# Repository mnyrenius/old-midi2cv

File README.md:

# old-midi2cv

PCB design + software for a midi2cv eurorack module.

I created it in 2016 and it has been installed in my rack since then.
It doesn't have any cool features and is probably really crappy, but it kind of works.

## Schematics

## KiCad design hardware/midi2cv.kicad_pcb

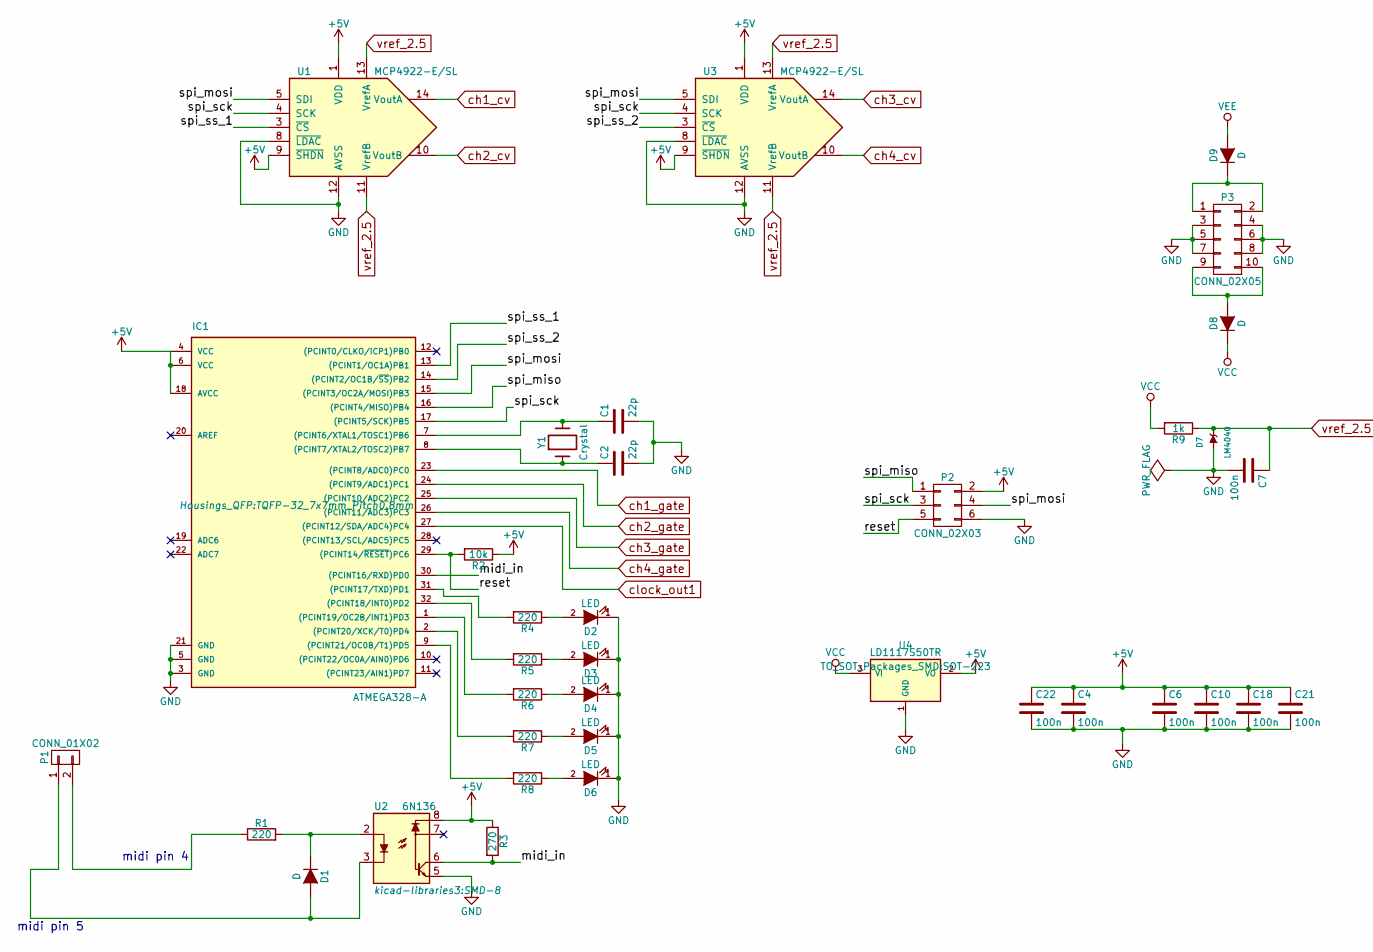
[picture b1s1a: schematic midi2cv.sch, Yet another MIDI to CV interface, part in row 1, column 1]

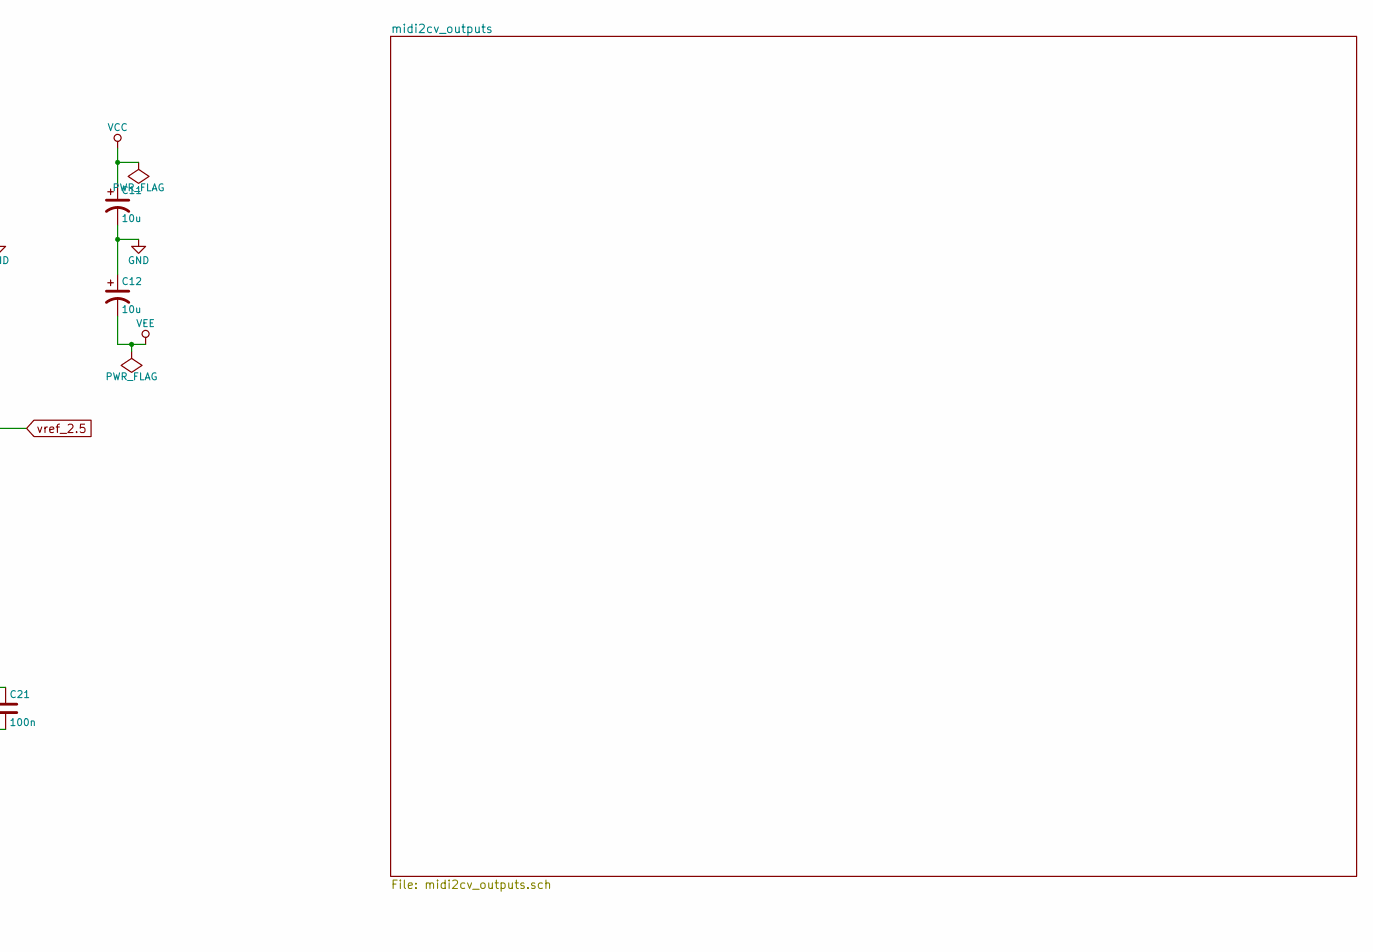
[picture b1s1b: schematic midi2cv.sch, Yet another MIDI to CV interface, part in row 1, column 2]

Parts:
C1, C2: 22p; C_0603_HandSoldering
C4, C6, C7, C10, C18, C21, C22: 100n; C_0603_HandSoldering
C11, C12: 10u; c_elec_4x5.3
D1, D8, D9: D; SOD123
D2, D3, D4, D5, D6: LED; LED-3MM
D7: LM4040; SOT-23
IC1: ATMEGA328-A; TQFP-32_7x7mm_Pitch0.8mm
P1: CONN_01X02; Pin_Header_Straight_1x02
P2: CONN_02X03; Pin_Header_Straight_2x03
P3: CONN_02X05; Pin_Header_Straight_2x05
R1, R4, R5, R6, R7, R8: 220; R_0603_HandSoldering
R2: 10k; R_0603_HandSoldering
R3: 270; R_0603_HandSoldering
R9: 1k; R_0603_HandSoldering
U1, U3: MCP4922-E/SL; SOIC-14_N
U2: 6N136; SMD-8
U4: LD1117S50TR; SOT-223
Y1: Crystal; Crystal_HC49-SD_SMD

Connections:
+5V: C4.1, C6.1, C10.1, C18.1, C21.1, C22.1, IC1.4 (VCC), IC1.6 (VCC), IC1.18 (AVCC), P2.2, R2.1, R3.1, U1.1 (VDD), U1.9 (~SHDN~), U2.8, U3.1 (VDD), U3.9 (~SHDN~), U4.2 (VO)
/midi_in: IC1.30 ((PCINT16/RXD)PD0), R3.2, U2.6
/reset: IC1.29 ((PCINT14/~RESET~)PC6), P2.5, R2.2
/spi_miso: IC1.16 ((PCINT4/MISO)PB4), P2.1
/spi_mosi: IC1.15 ((PCINT3/OC2A/MOSI)PB3), P2.4, U1.5 (SDI), U3.5 (SDI)
/spi_sck: IC1.17 ((PCINT5/SCK)PB5), P2.3, U1.4 (SCK), U3.4 (SCK)
/spi_ss_1: IC1.13 ((PCINT1/OC1A)PB1), U1.3 (~CS~)
/spi_ss_2: IC1.14 ((PCINT2/OC1B/~SS~)PB2), U3.3 (~CS~)
GND: C1.2, C2.2, C4.2, C6.2, C7.2, C10.2, C11.2, C12.1, C18.2, C21.2, C22.2, D2.1 (K), D3.1 (K), D4.1 (K), D5.1 (K), D6.1 (K), D7.2 (A), IC1.3 (GND), IC1.5 (GND), IC1.21 (GND), P2.6, P3.3, P3.4, P3.5, P3.6, P3.7, P3.8, U1.8 (~LDAC~), U1.12 (AVSS), U2.5, U3.8 (~LDAC~), U3.12 (AVSS), U4.1 (GND); also elsewhere on the board
unnamed: C1.1, IC1.7 ((PCINT6/XTAL1/TOSC1)PB6), Y1.2
unnamed: C2.1, IC1.8 ((PCINT7/XTAL2/TOSC2)PB7), Y1.1
unnamed: D1.1 (K), R1.2, U2.2
unnamed: D1.2 (A), P1.1, U2.3
unnamed: D2.2 (A), R4.1
unnamed: D3.2 (A), R5.1
unnamed: D4.2 (A), R6.1
unnamed: D5.2 (A), R7.1
unnamed: D6.2 (A), R8.1
unnamed: D8.2 (A), P3.9, P3.10
unnamed: D9.1 (K), P3.1, P3.2
unnamed: IC1.1 ((PCINT19/OC2B/INT1)PD3), R6.2
unnamed: IC1.2 ((PCINT20/XCK/T0)PD4), R7.2
unnamed: IC1.9 ((PCINT21/OC0B/T1)PD5), R8.2
unnamed: IC1.31 ((PCINT17/TXD)PD1), R4.2
unnamed: IC1.32 ((PCINT18/INT0)PD2), R5.2
unnamed: P1.2, R1.1
VCC: C11.1, D8.1 (K), R9.2, U4.3 (VI); also elsewhere on the board
VEE: C12.2, D9.2 (A); also elsewhere on the board
ch1_cv: U1.14 (VoutA); also elsewhere on the board
ch1_gate: IC1.23 ((PCINT8/ADC0)PC0); also elsewhere on the board
ch2_cv: U1.10 (VoutB); also elsewhere on the board
ch2_gate: IC1.24 ((PCINT9/ADC1)PC1); also elsewhere on the board
ch3_cv: U3.14 (VoutA); also elsewhere on the board
ch3_gate: IC1.25 ((PCINT10/ADC2)PC2); also elsewhere on the board
ch4_cv: U3.10 (VoutB); also elsewhere on the board
ch4_gate: IC1.26 ((PCINT11/ADC3)PC3); also elsewhere on the board
clock_out1: IC1.27 ((PCINT12/SDA/ADC4)PC4); also elsewhere on the board
vref_2.5: C7.1, D7.1 (K), R9.1, U1.11 (VrefB), U1.13 (VrefA), U3.11 (VrefB), U3.13 (VrefA); also elsewhere on the board

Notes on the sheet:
midi pin 4
midi pin 5

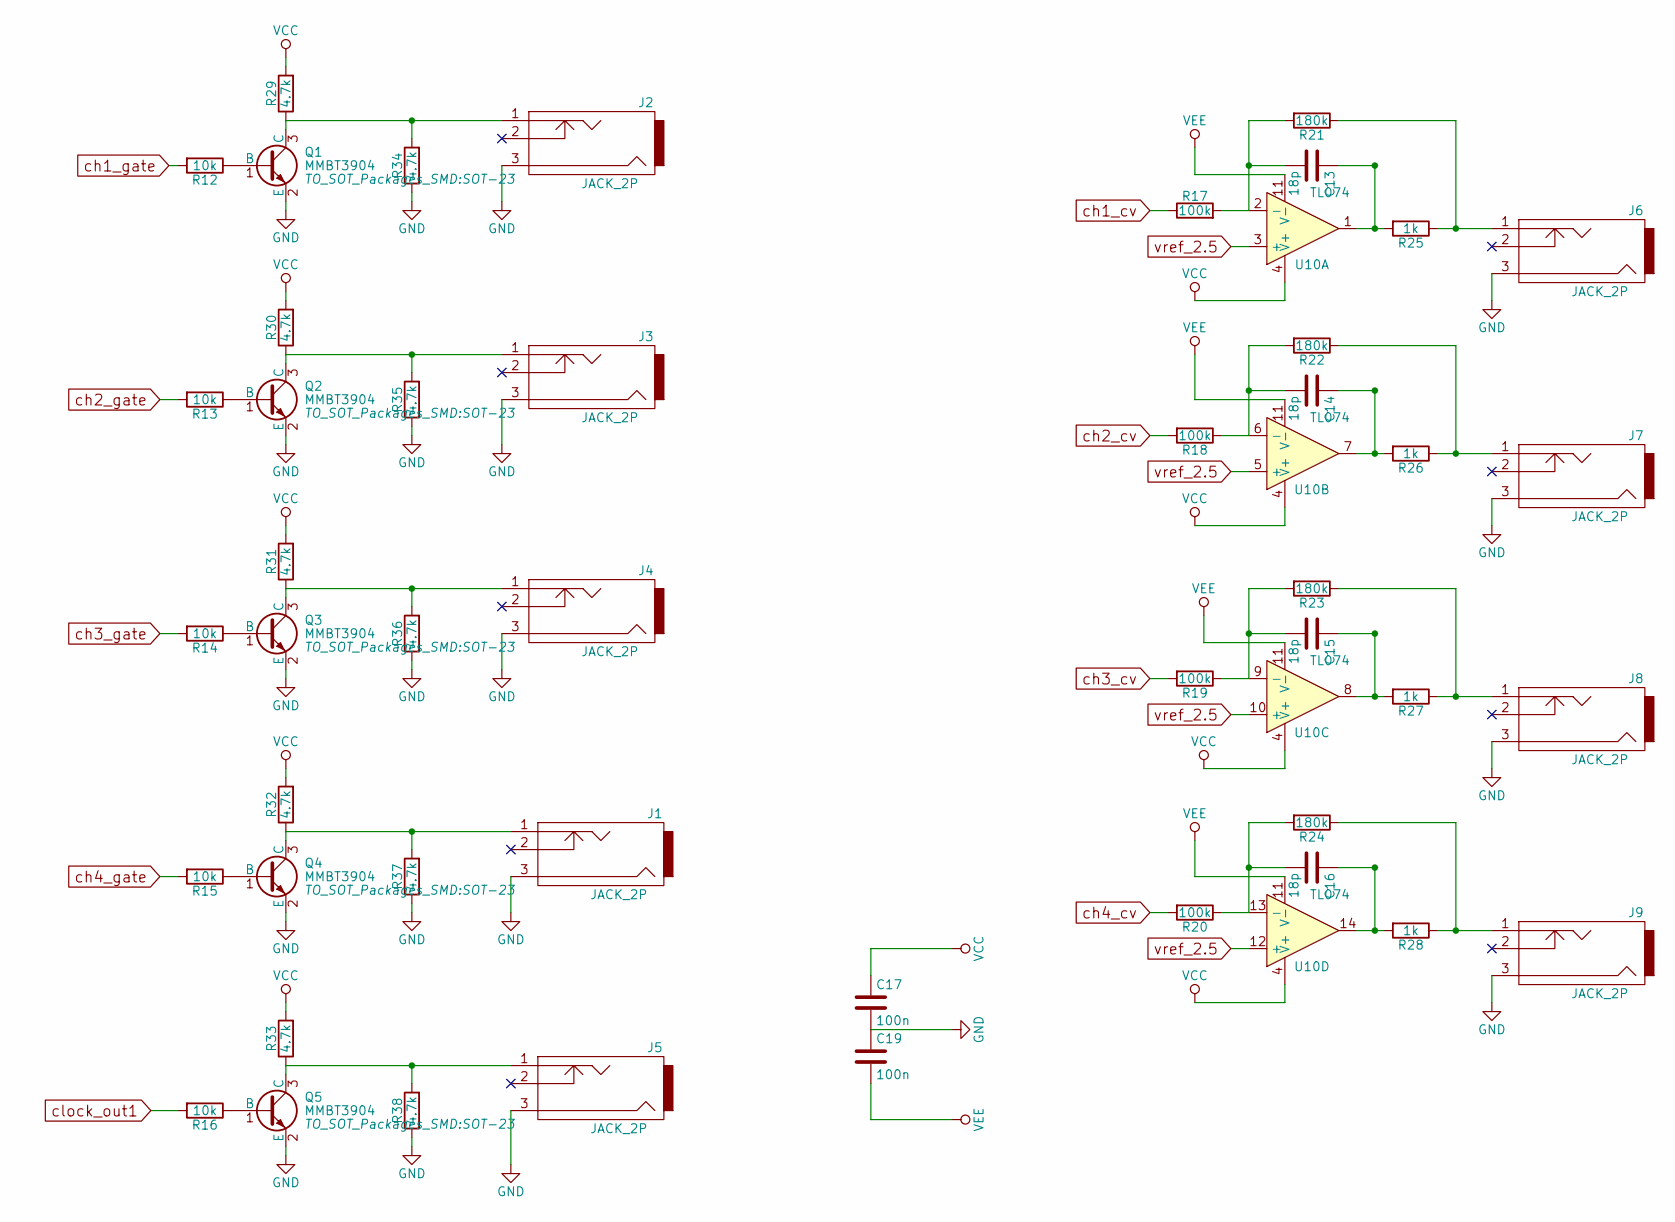
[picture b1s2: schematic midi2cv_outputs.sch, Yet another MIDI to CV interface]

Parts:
C13, C14, C15, C16: 18p; C_0603_HandSoldering
C17, C19: 100n; C_0603_HandSoldering
J1, J2, J3, J4, J5, J6, J7, J8, J9: JACK_2P; THONKICONN2
Q1, Q2, Q3, Q4, Q5: MMBT3904; SOT-23
R12, R13, R14, R15, R16: 10k; R_0603_HandSoldering
R17, R18, R19, R20: 100k; R_0603_HandSoldering
R21, R22, R23, R24: 180k; R_0603_HandSoldering
R25, R26, R27, R28: 1k; R_0603_HandSoldering
R29, R30, R31, R32, R33, R34, R35, R36, R37, R38: 4.7k; R_0603_HandSoldering
U10: TL074; SOIC-14_N

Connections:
GND: C17.2, C19.1, J1.3, J2.3, J3.3, J4.3, J5.3, J6.3, J7.3, J8.3, J9.3, Q1.2 (E), Q2.2 (E), Q3.2 (E), Q4.2 (E), Q5.2 (E), R34.1, R35.1, R36.1, R37.1, R38.1; also elsewhere on the board
unnamed: C13.1, R25.2, U10.1
unnamed: C13.2, R17.2, R21.2, U10.2 (-)
unnamed: C14.1, R26.2, U10.7
unnamed: C14.2, R18.1, R22.2, U10.6 (-)
unnamed: C15.1, R27.2, U10.8
unnamed: C15.2, R19.1, R23.2, U10.9 (-)
unnamed: C16.1, R28.2, U10.14
unnamed: C16.2, R20.1, R24.2, U10.13 (-)
unnamed: J1.1, Q4.3 (C), R32.1, R37.2
unnamed: J2.1, Q1.3 (C), R29.1, R34.2
unnamed: J3.1, Q2.3 (C), R30.1, R35.2
unnamed: J4.1, Q3.3 (C), R31.1, R36.2
unnamed: J5.1, Q5.3 (C), R33.1, R38.2
unnamed: J6.1, R21.1, R25.1
unnamed: J7.1, R22.1, R26.1
unnamed: J8.1, R23.1, R27.1
unnamed: J9.1, R24.1, R28.1
unnamed: Q1.1 (B), R12.1
unnamed: Q2.1 (B), R13.1
unnamed: Q3.1 (B), R14.1
unnamed: Q4.1 (B), R15.1
unnamed: Q5.1 (B), R16.1
VCC: C17.1, R29.2, R30.2, R31.2, R32.2, R33.2, U10.4 (V+); also elsewhere on the board
VEE: C19.2, U10.11 (V-); also elsewhere on the board
ch1_cv: R17.1; also elsewhere on the board
ch1_gate: R12.2; also elsewhere on the board
ch2_cv: R18.2; also elsewhere on the board
ch2_gate: R13.2; also elsewhere on the board
ch3_cv: R19.2; also elsewhere on the board
ch3_gate: R14.2; also elsewhere on the board
ch4_cv: R20.2; also elsewhere on the board
ch4_gate: R15.2; also elsewhere on the board
clock_out1: R16.2; also elsewhere on the board
vref_2.5: U10.3 (+), U10.5 (+), U10.10 (+), U10.12 (+); also elsewhere on the board

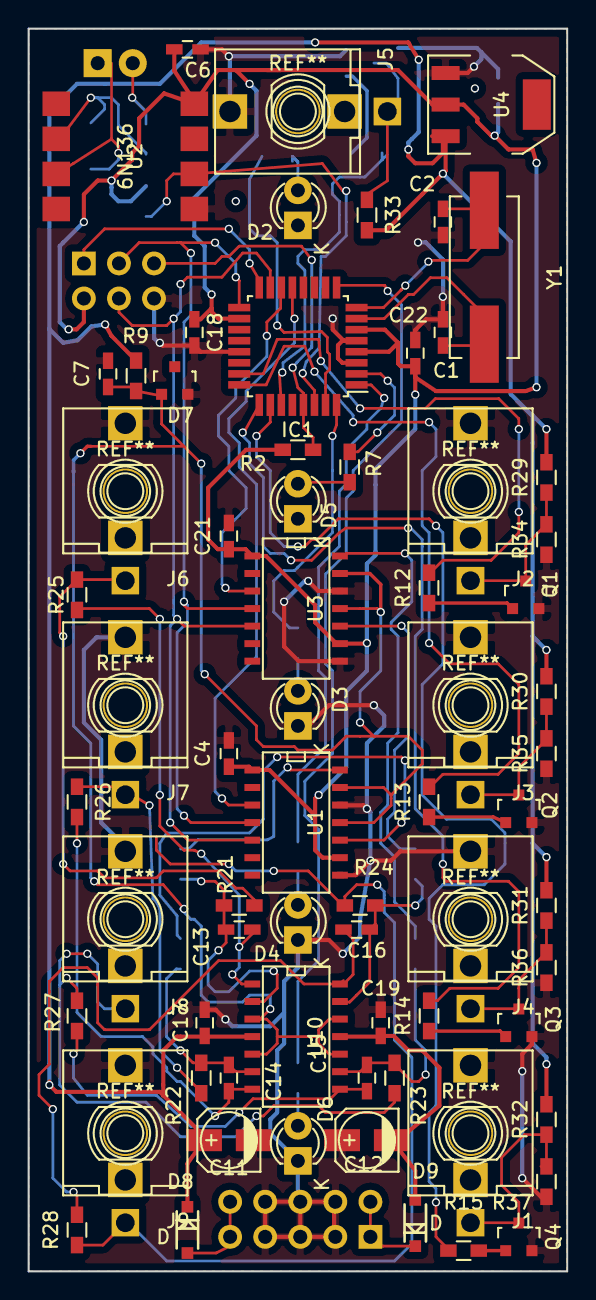
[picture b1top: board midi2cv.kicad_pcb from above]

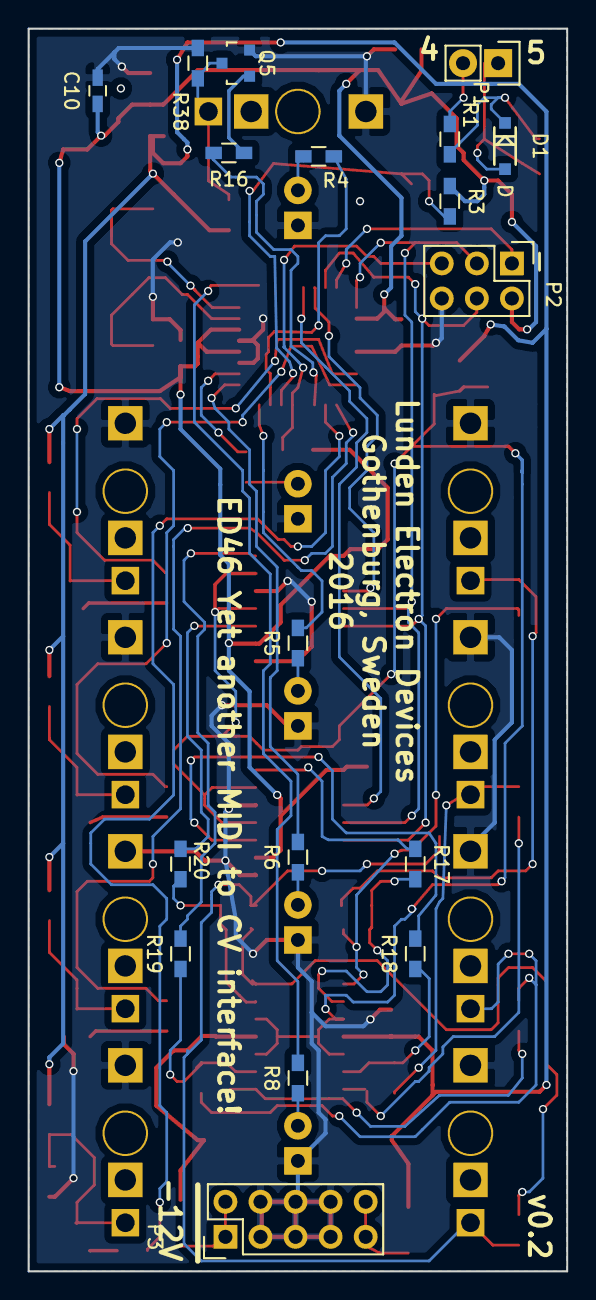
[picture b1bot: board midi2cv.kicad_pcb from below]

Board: 2 copper layers, 39.0 x 90.0 mm, 86 parts (18 on the bottom side), 60 nets.

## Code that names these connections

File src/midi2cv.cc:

#include "dac.h"
#include "uart.h"
#include "midi.h"
#include "ringbuffer.h"

#include <avr/io.h>
#include <avr/interrupt.h>
#include <util/delay.h>
#include <stdlib.h>
   
/* ---------- PIN CONFIGURATION ----------
 *
 * PORTB
 *  1 - mcp4922 1 slave select
 *  2 - mcp4922 2 slave select
 *  5 - mcp4922 sck
 *  3 - mcp4922 mosi
 *  
 * PORTC
 *  0 - gate channel 1
 *  1 - gate channel 2 
 *  2 - gate channel 3 
 *  3 - gate channel 4 
 *  4 - clock 1 
 *
 * PORTD
 *  0 - midi in
 *  1 - led D2
 *  2 - led D3
 *  3 - led D4
 *  4 - led D5
 *  5 - led D6
 *
 * ------------------------------------ */


/* --------- CV OUTPUT STAGE NOTES ---------
 *
 * V_out = - V_dac (R1/R2) + V_ref ((R1+R2)/R1)
 *
 * R1 = 100k
 * R2 = 180k
 *
 * ------------------------------------ */

const uint8_t  NUM_CHANNELS         = 4;
const uint8_t  NUM_OCTAVES          = 10;
const uint8_t  NUM_STEPS_PER_OCTAVE = 12;
const uint16_t NUM_DAC_VALUES       = 4096;

struct channel_t
{
  int32_t  cv;
  bool     gate_on;
  int32_t  pitch_bend;
  int32_t  calibration_offsets[10];
};
 
namespace bit
{

inline void set (volatile uint8_t & port, uint8_t bit)
{
  port |= _BV (bit);
}

inline void clear (volatile uint8_t & port, uint8_t bit)
{
  port &= ~ _BV (bit);
}

}

uint16_t   _dac_values[120];

struct Gate
{
  struct port_config
  {
    volatile uint8_t & port;
    uint8_t            pin[4];
  };

  struct config
  {
    port_config gate_config;
    port_config led_config;
  };

  Gate (const config & c)
    : _config (c)
  {
  }

  void on (uint16_t channel)
  {
    auto gconf = _config.gate_config;
    bit::clear (gconf.port, gconf.pin[channel]);
 
    auto lconf = _config.led_config;
    bit::set (lconf.port, lconf.pin[channel]); 
  }

  void off (uint16_t channel)
  {
    auto gconf = _config.gate_config;
    bit::set (gconf.port, gconf.pin[channel]);
 
    auto lconf = _config.led_config;
    bit::clear (lconf.port, lconf.pin[channel]);  
  }

  config _config;
};

void generate_dac_values (uint16_t * values)
{
  for (uint16_t i = 0; i < 120; ++i)
  {
    values[i] = 4096 - 38 * i;
  }
}
  
uint16_t midi_note_to_cv (
        uint16_t * values,
        uint8_t note)
    {
      if (note >= 0 && note < 120)
      {
        return values[note];
      }

      else
      {
        return 1024;
      }
    } 

void output_channels (
    channel_t * channels,
    Dac & dac,
    Gate & gate)
{
  for (uint16_t i = 0; i < NUM_CHANNELS; ++i)
  {
    auto & channel = channels[i];
    dac.write (i, channel.cv + channel.pitch_bend);
    if (channel.gate_on)
    {
      gate.on (i);
    }

    else
    {
      gate.off (i);
    }
  }
}
  
struct MidiHandler
{
  using data = channel_t;

  static void note_on (channel_t * channels, uint8_t channel, uint8_t note)
  {
    auto & ch = channels[channel];

    ch.cv = 
      midi_note_to_cv (_dac_values, note) +
      ch.calibration_offsets[note/12];

    ch.gate_on = true;
  }

  static void note_off (channel_t * channels, uint8_t channel)
  {
    channels[channel].gate_on = false;
  }

  static void pitch_bend (channel_t * channels, uint8_t channel, int32_t value)
  {
    constexpr auto scale = 0x4000 / 24 / 38;
    int32_t bend = (8192 - value) / scale;
    channels[channel].pitch_bend = bend;
  }
  
  static void clock (uint8_t counter)
  {
    switch (counter)
    {
      case 0:
      case 12:
        PORTC &= ~ _BV (PC4);
        PORTD |= _BV (PD1);
        break;

      case 6:
      case 18:
      case 255: // Stop
        PORTC |= _BV (PC4);
        PORTD &= ~ _BV (PD1);
        break;

      default:
        break;
    }
  }
};    

int main ()
{
  // Setup gate and clock outputs
  DDRC  |= _BV (PC0) | _BV (PC1) | _BV (PC2) | _BV (PC3) | _BV (PC4);
  PORTC |= _BV (PC0) | _BV (PC1) | _BV (PC2) | _BV (PC3) | _BV (PC4); 

  // Setup leds
  DDRD |= _BV (PD1) | _BV (PD2) | _BV (PD3) | _BV (PD4) | _BV (PD5);
  PORTD &= ~ 0x3e;
  
  Dac dac;
  Gate::config c
  {
    {
      PORTC,
      {
        PC0,
        PC1,
        PC2,
        PC3,
      }
    },
    {
      PORTD,
      {
        PD4,
        PD2,
        PD3,
        PD5,
      }
    },
  };

  Gate gate (c);

  generate_dac_values (_dac_values);
  channel_t channels[NUM_CHANNELS];
  
  for (int i = 0; i < NUM_CHANNELS; ++i)
  {
    channels[i].cv = 0;
    channels[i].gate_on = false;
    channels[i].pitch_bend = 0;

    for (int j = 0; j < 10; ++j)
    {
      channels[i].calibration_offsets[j] = 0;
    }
  }

  Uart serial;

  Midi<MidiHandler> midi (channels, serial);

  sei ();

  while (true)
  {
    midi.process_next ();
    output_channels (channels, dac, gate);
  }
}

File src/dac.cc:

#include "dac.h"
#include "avr_types.h"

#include <avr/io.h>

Dac::Dac ()
{
  // Setup slave selects, sck and mosi
  DDRB |= _BV (PB1) | _BV (PB2) | _BV (PB3) | _BV (PB5);
 
  // Enable spi, master mode, fcpu / 64
  SPSR = 0;
  SPCR = _BV (SPE) | _BV (MSTR) | _BV (SPR1); 

  _config[0].slave_select = PB1;
  _config[0].dac_command  = 0x10;

  _config[1].slave_select = PB1;
  _config[1].dac_command  = 0x90;

  _config[2].slave_select = PB2;
  _config[2].dac_command  = 0x10;

  _config[3].slave_select = PB2;
  _config[3].dac_command  = 0x90;
}

Dac::~Dac ()
{
}

void Dac::write (uint8_t channel, uint16_t value)
{
  auto config = _config[channel];

  PORTB &= ~ _BV (config.slave_select);

  SPDR = (config.dac_command & 0xf0) | (0x0f & (value >> 8));
  while (!(SPSR & (1 << SPIF)));

  SPDR = value & 0x00ff;
  while (!(SPSR & (1 << SPIF)));

  PORTB |= _BV (config.slave_select);
}

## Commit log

2020-12-23 Copied files from old backup
2020-12-23 Add schematics svg
